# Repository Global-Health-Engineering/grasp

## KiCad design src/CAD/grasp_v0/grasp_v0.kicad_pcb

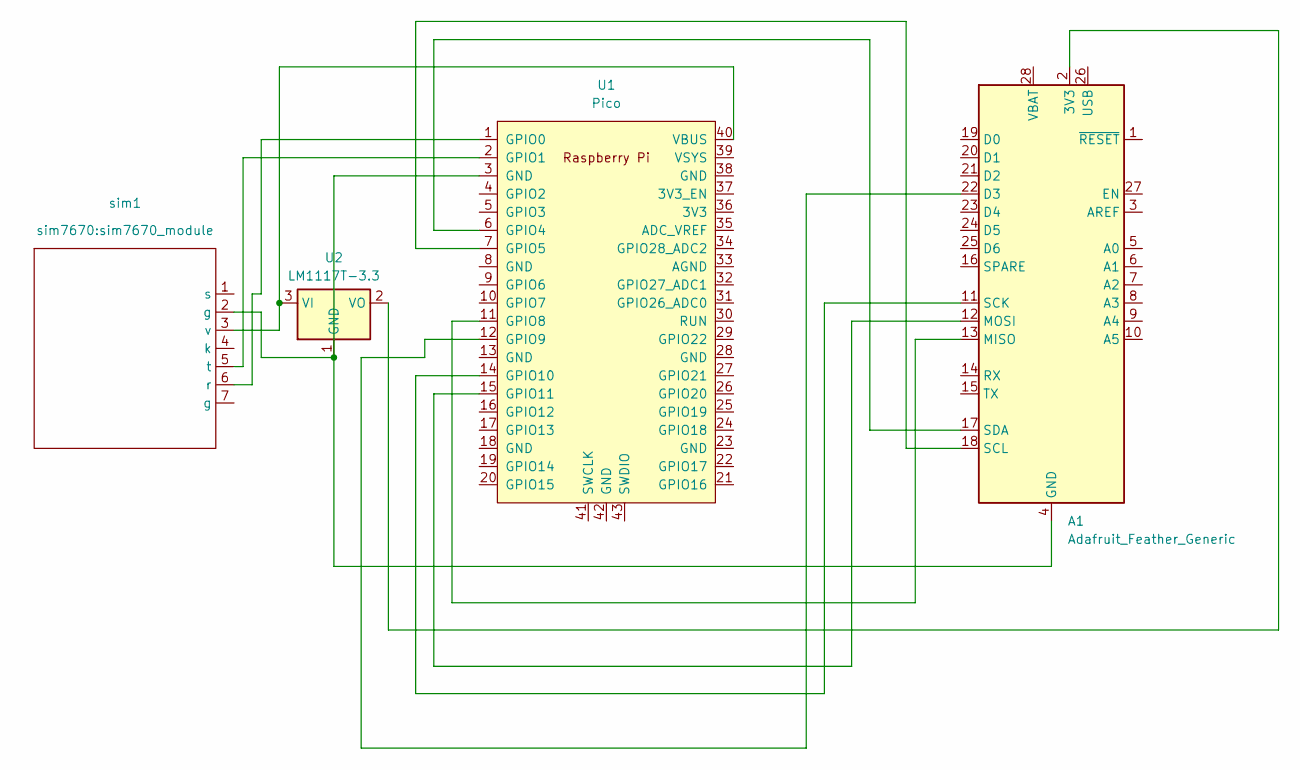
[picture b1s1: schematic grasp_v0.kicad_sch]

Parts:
A1: Adafruit_Feather_Generic; Adafruit_Feather
U1: Pico; RPi_Pico_SMD_TH
U2: LM1117T-3.3; TO-220-3_Vertical
sim1: sim7670_module

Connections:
unnamed: A1.2 (3V3), U2.2 (VO)
unnamed: A1.22 (D3), U1.12 (GPIO9)
unnamed: A1.4 (GND), U1.3 (GND), U2.1 (GND), sim1.2 (g)
unnamed: A1.13 (MISO), U1.11 (GPIO8)
unnamed: A1.12 (MOSI), U1.15 (GPIO11)
unnamed: A1.11 (SCK), U1.14 (GPIO10)
unnamed: A1.18 (SCL), U1.7 (GPIO5)
unnamed: A1.17 (SDA), U1.6 (GPIO4)
unnamed: U1.1 (GPIO0), sim1.6 (r)
unnamed: U1.2 (GPIO1), sim1.5 (t)
unnamed: U1.40 (VBUS), U2.3 (VI), sim1.3 (v)

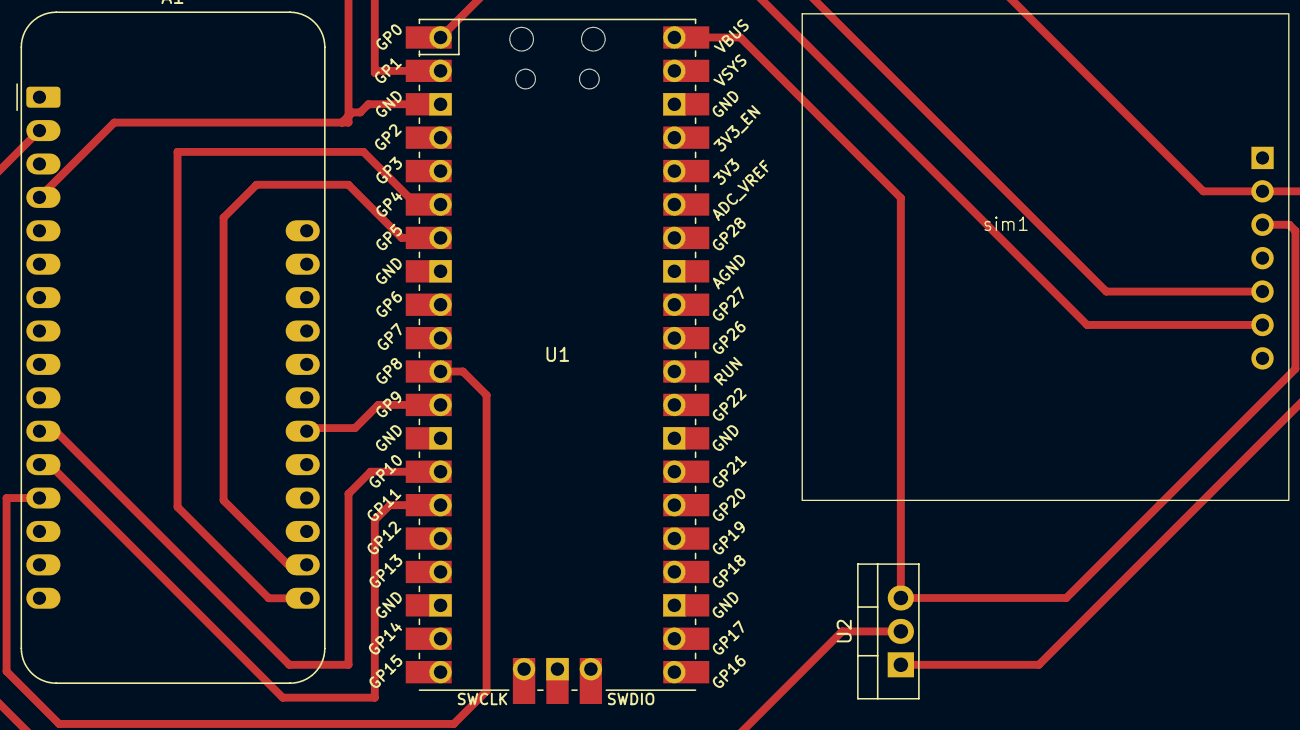
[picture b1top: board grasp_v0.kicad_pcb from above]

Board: 2 copper layers, 4 parts (0 on the bottom side), 11 nets.

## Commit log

2024-10-31 sim7080g testing + raspberry pi doc
2024-11-16 gps connectivity testing data
2024-11-21 Added tests + synced with publifone
2024-12-01 test code, pcb design
2024-12-06 Folder reorg + new PCB and SPICE files
2024-12-06 reorg
2024-12-07 documentation
2024-12-13 update all
2024-12-23 DENIZ files
2024-12-23 gen_update
